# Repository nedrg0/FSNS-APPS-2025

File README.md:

# FSNS-APPS-2025
Accelerator pedal position sensor interface board for a Formumla Student vehicle.

# Main Features
- Reads signals from two linear displacement sesnors and checks for implausability,
- Realy output if a fault is detected,
- CAN Communication

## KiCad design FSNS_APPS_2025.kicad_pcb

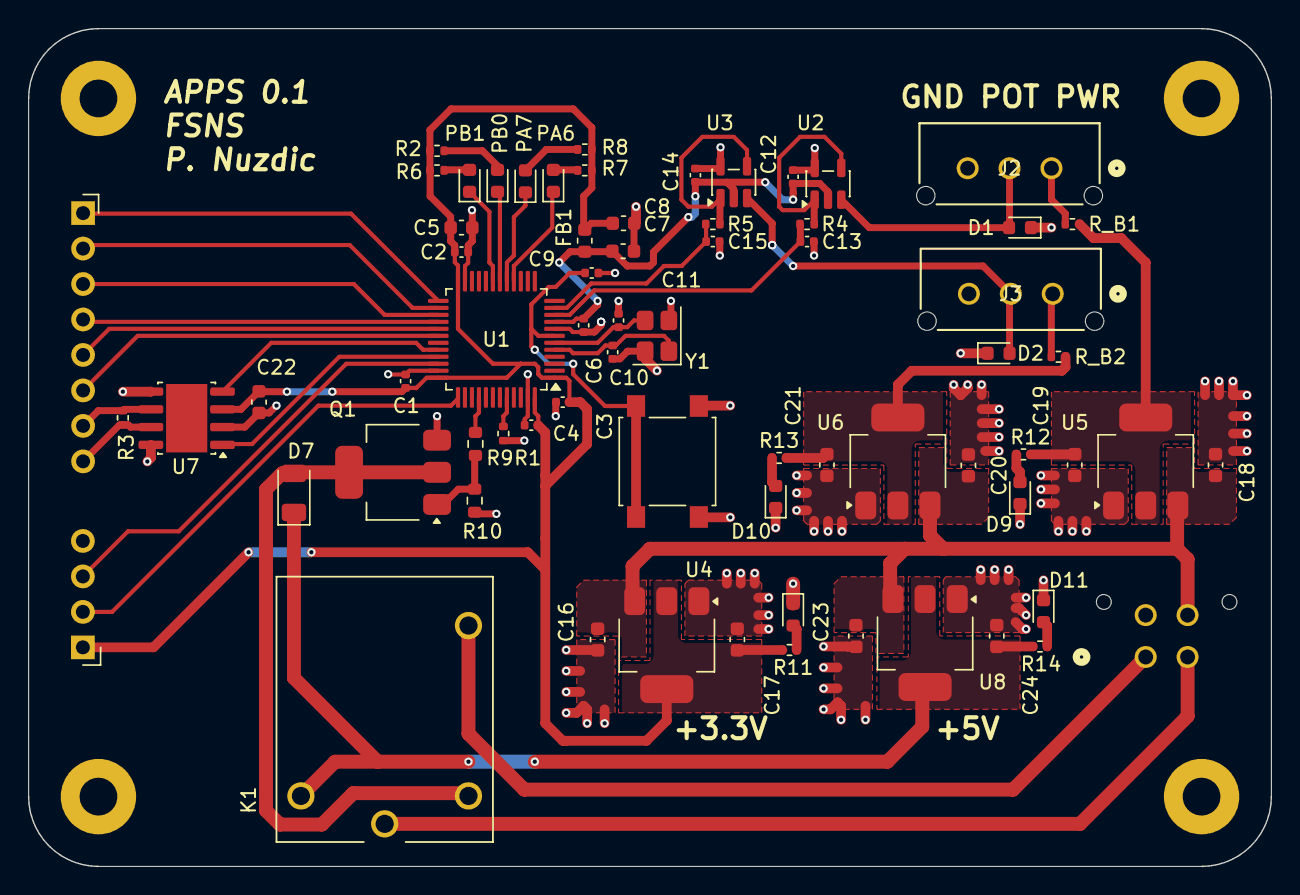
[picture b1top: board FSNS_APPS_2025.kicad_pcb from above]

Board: 2 copper layers, 89.0 x 60.0 mm, 73 parts (1 on the bottom side), 48 nets.

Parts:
C1, C2, C3, C4, C9, C12, C13, C14, C15: 100n; C_0402_1005Metric
C5: 10u; C_0603_1608Metric
C6: 10n; C_0402_1005Metric
C7, C8, C16, C18, C20, C23: 1u; C_0603_1608Metric
C10, C11: 10p; C_0402_1005Metric
C17, C19, C21, C24: 2.2u; C_0603_1608Metric
C22: 100n; C_0603_1608Metric
D1, D2: D_TVS; D_0603_1608Metric
D7: D; D_1206_3216Metric
D8, D9, D10, D11: LED; LED_0603_1608Metric
FB1: 120R; L_0603_1608Metric
H1, H2, H3, H4: MountingHole_Pad; MountingHole_2.7mm_Pad
J1: Conn_01x04_Pin; CONN_SD-43045-005_04_MOL
J2, J3: Conn_01x03_Pin; CONN_SD-43650-006_03_MOL
J4: Conn_01x04_Pin; PinHeader_1x04_P2.54mm_Horizontal
J5: Conn_01x08_Pin; PinSocket_1x08_P2.54mm_Horizontal
K1: PR12-12V-360-1A; RELAY_PR12-12V-360-1A
PA6, PA7: LED; LED_0603_1608Metric
PB0, PB1: LED; LED_0603_1608Metric
Q1: NDT3055L; SOT-223-3_TabPin2
R1: 10k; R_0402_1005Metric
R2, R6, R7, R8, R11, R12, R13, R14: 1K; R_0402_1005Metric
R3: 120R; R_0402_1005Metric
R4, R5: 4k7; R_0402_1005Metric
R9: 100R; R_0603_1608Metric
R10: 10K; R_0603_1608Metric
R_B1: 100R; R_0402_1005Metric
R_B2: 330R; R_0402_1005Metric
SW1: SW_Push; SW_SPST_B3S-1000
U1: STM32F103C8T6; LQFP-48_7x7mm_P0.5mm
U2, U3: MCP6001-OT; SOT-23-5
U4, U5, U6, U8: LM1117-Q1; SOT-223-3_TabPin2
U7: TCAN3404-Q1; SOIC-8-1EP_3.9x4.9mm_P1.27mm_EP2.95x4.9mm_Mask2.71x3.4mm
Y1: 16MHz; Crystal_SMD_3225-4Pin_3.2x2.5mm

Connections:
+3.3V: C1.1, C2.1, C3.1, C4.1, C5.1, C8.1, C17.1, C22.1, FB1.2, J4.1, R2.2, R6.2, R7.2, R8.2, R11.2, U1.1 (VBAT), U1.24 (VDD), U1.36 (VDD), U1.48 (VDD), U4.2 (OUT), U7.3 (VCC)
+3.3VA: C6.1, C7.1, C12.1, C14.1, FB1.1, U1.9 (VDDA), U2.2 (V-), U3.2 (V-)
+3.3V_POT1: C19.1, R12.2, R_B1.1, U5.2 (OUT)
+3.3V_POT2: C21.1, R13.2, R_B2.1, U6.2 (OUT)
+5V: C24.1, D7.1 (K), K1.A1, R14.2, U8.2 (OUT)
+12V: C16.1, C18.1, C20.1, C23.1, J1.4, U4.3 (IN), U5.3 (IN), U6.3 (IN), U8.3 (IN)
/APPS1_OUT: C13.2, R4.2, U1.10 (PA0)
/APPS2_OUT: C15.2, R5.2, U1.11 (PA1)
/APPS_SDC_IN: J1.2, K1.COM
/APPS_SDC_OUT: J1.1, K1.NO
/BOOT0: R1.2, U1.44 (BOOT0)
/CANH: J5.8, R3.1, U7.7 (CANH)
/CANL: J5.7, R3.2, U7.6 (CANL)
/CAN_RX: U1.32 (PA11), U7.4 (RXD)
/CAN_TX: U1.33 (PA12), U7.1 (TXD)
/LED_DBG_1: PB0.1 (K), U1.18 (PB0)
/LED_DBG_2: PB1.1 (K), U1.19 (PB1)
/LED_DBG_3: PA6.1 (K), U1.16 (PA6)
/LED_DBG_4: PA7.1 (K), U1.17 (PA7)
/NRST: C9.1, SW1.2, U1.7 (NRST)
/OSC_IN: C10.1, U1.5 (PD0), Y1.1
/OSC_OUT: C11.1, U1.6 (PD1), Y1.3
/PA8: J5.5, U1.29 (PA8)
/PA9: J5.6, U1.30 (PA9)
/PB12: J5.1, U1.25 (PB12)
/PB13: J5.2, U1.26 (PB13)
/PB14: J5.3, U1.27 (PB14)
/PB15: J5.4, U1.28 (PB15)
/POT1: D1.2 (A2), J2.2, U2.3 (+)
/POT2: D2.2 (A2), J3.2, U3.3 (+)
/RLY_EN: R9.1, U1.40 (PB4)
/SWCLK: J4.2, U1.37 (PA14)
/SWDIO: J4.3, U1.34 (PA13)
GND: C1.2, C2.2, C3.2, C4.2, C5.2, C6.2, C7.2, C8.2, C9.2, C10.2, C11.2, C12.2, C13.1, C14.2, C15.1, C16.2, C17.2, C18.2, C19.2, C20.2, C21.2, C22.2, C23.2, C24.2, D1.1 (A1), D2.1 (A1), D8.1 (K), D9.1 (K), D10.1 (K), D11.1 (K), H1.1, H2.1, H3.1, H4.1, J1.3, J2.3, J3.3, J4.4, Q1.3 (S), R1.1, R10.2, SW1.1, U1.8 (VSSA), U1.23 (VSS), U1.35 (VSS), U1.47 (VSS), U2.5 (V+), U3.5 (V+), U4.1 (GND), U5.1 (GND), U6.1 (GND), U7.2 (GND), U7.5 (SHDN/VIO), U7.8 (STB), U8.1 (GND), Y1.2, Y1.4
unnamed: PB0.2 (A), R2.1
unnamed: PB1.2 (A), R6.1
unnamed: PA6.2 (A), R7.1
unnamed: PA7.2 (A), R8.1
unnamed: D7.2 (A), K1.A2, Q1.2 (D)
unnamed: D8.2 (A), R11.1
unnamed: D9.2 (A), R12.1
unnamed: D10.2 (A), R13.1
unnamed: D11.2 (A), R14.1
unnamed: J2.1, R_B1.2
unnamed: J3.1, R_B2.2
unnamed: Q1.1 (G), R9.2, R10.1
unnamed: R4.1, U2.1, U2.4 (-)
unnamed: R5.1, U3.1, U3.4 (-)

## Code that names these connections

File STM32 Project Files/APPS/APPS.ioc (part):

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Mcu.Name=STM32F103C(8-B)Tx
Mcu.Package=LQFP48
Mcu.UserName=STM32F103C8Tx
PA0-WKUP.Signal=ADCx_IN0
PA1.Signal=ADCx_IN1
PA10.Signal=GPIO_Output
PA11.Mode=CAN_Activate
PA11.Signal=CAN_RX
PA12.Mode=CAN_Activate
PA12.Signal=CAN_TX
PA13.Mode=Serial_Wire
PA13.Signal=SYS_JTMS-SWDIO
PA14.Mode=Serial_Wire
PA14.Signal=SYS_JTCK-SWCLK
PA6.GPIOParameters=PinState,GPIO_PuPd,GPIO_ModeDefaultOutputPP
PA6.GPIO_ModeDefaultOutputPP=GPIO_MODE_OUTPUT_PP
PA6.GPIO_PuPd=GPIO_PULLDOWN
PA6.PinState=GPIO_PIN_RESET
PA6.Signal=GPIO_Output
PA7.GPIOParameters=PinState,GPIO_PuPd,GPIO_ModeDefaultOutputPP
PA7.GPIO_ModeDefaultOutputPP=GPIO_MODE_OUTPUT_PP
PA7.GPIO_PuPd=GPIO_PULLDOWN
PA7.PinState=GPIO_PIN_RESET
PA7.Signal=GPIO_Output
PA8.Signal=GPIO_Output
PA9.Signal=GPIO_Output
PB0.GPIOParameters=PinState,GPIO_PuPd,GPIO_ModeDefaultOutputPP
PB0.GPIO_ModeDefaultOutputPP=GPIO_MODE_OUTPUT_PP
PB0.GPIO_PuPd=GPIO_PULLDOWN
PB0.PinState=GPIO_PIN_RESET
PB0.Signal=GPIO_Output
PB1.GPIOParameters=PinState,GPIO_PuPd,GPIO_ModeDefaultOutputPP
PB1.GPIO_ModeDefaultOutputPP=GPIO_MODE_OUTPUT_PP
PB1.GPIO_PuPd=GPIO_PULLDOWN
PB1.PinState=GPIO_PIN_RESET
PB1.Signal=GPIO_Output
PB12.Signal=GPIO_Output
PB13.Signal=GPIO_Output
PB14.Signal=GPIO_Output
PB15.Signal=GPIO_Output
PB4.GPIOParameters=PinState,GPIO_PuPd,GPIO_ModeDefaultOutputPP
PB4.GPIO_ModeDefaultOutputPP=GPIO_MODE_OUTPUT_OD
PB4.GPIO_PuPd=GPIO_PULLUP
PB4.PinState=GPIO_PIN_SET
PB4.Signal=GPIO_Output
PD0-OSC_IN.Mode=HSE-External-Oscillator
PD0-OSC_IN.Signal=RCC_OSC_IN
PD1-OSC_OUT.Mode=HSE-External-Oscillator
PD1-OSC_OUT.Signal=RCC_OSC_OUT
RCC.HSEDivPLL=RCC_HSE_PREDIV_DIV2
RCC.HSE_VALUE=16000000
RCC.SYSCLKFreq_VALUE=72000000
RCC.SYSCLKSource=RCC_SYSCLKSOURCE_PLLCLK
board=custom

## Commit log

2025-12-30 init
2025-12-30 Added signal-models readme
2026-01-03 Added LTSpice model for analog input stage
2026-01-04 Added analog signal conditioning to schematic. AddedAPPS System FBD.
2026-01-05 Added a few components.
2026-01-06 Finisished most of the schematic.
2026-01-06 Added a few PCB parts.
2026-01-07 Added mouting holes and test points.
2026-01-11 Updated schematic and PCB.
2026-01-13 Schematic and PCB v0.1
2026-01-14 Small Changes
2026-01-18 APPS Project
2026-01-18 Repo cleanup
2026-01-18 Fixed unconnected footprints
